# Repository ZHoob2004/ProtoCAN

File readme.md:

# ProtoCAN
A simple CAN interface for breadboards using MCP2515 controller and MCP2562 transciever.

(formerly canbus)

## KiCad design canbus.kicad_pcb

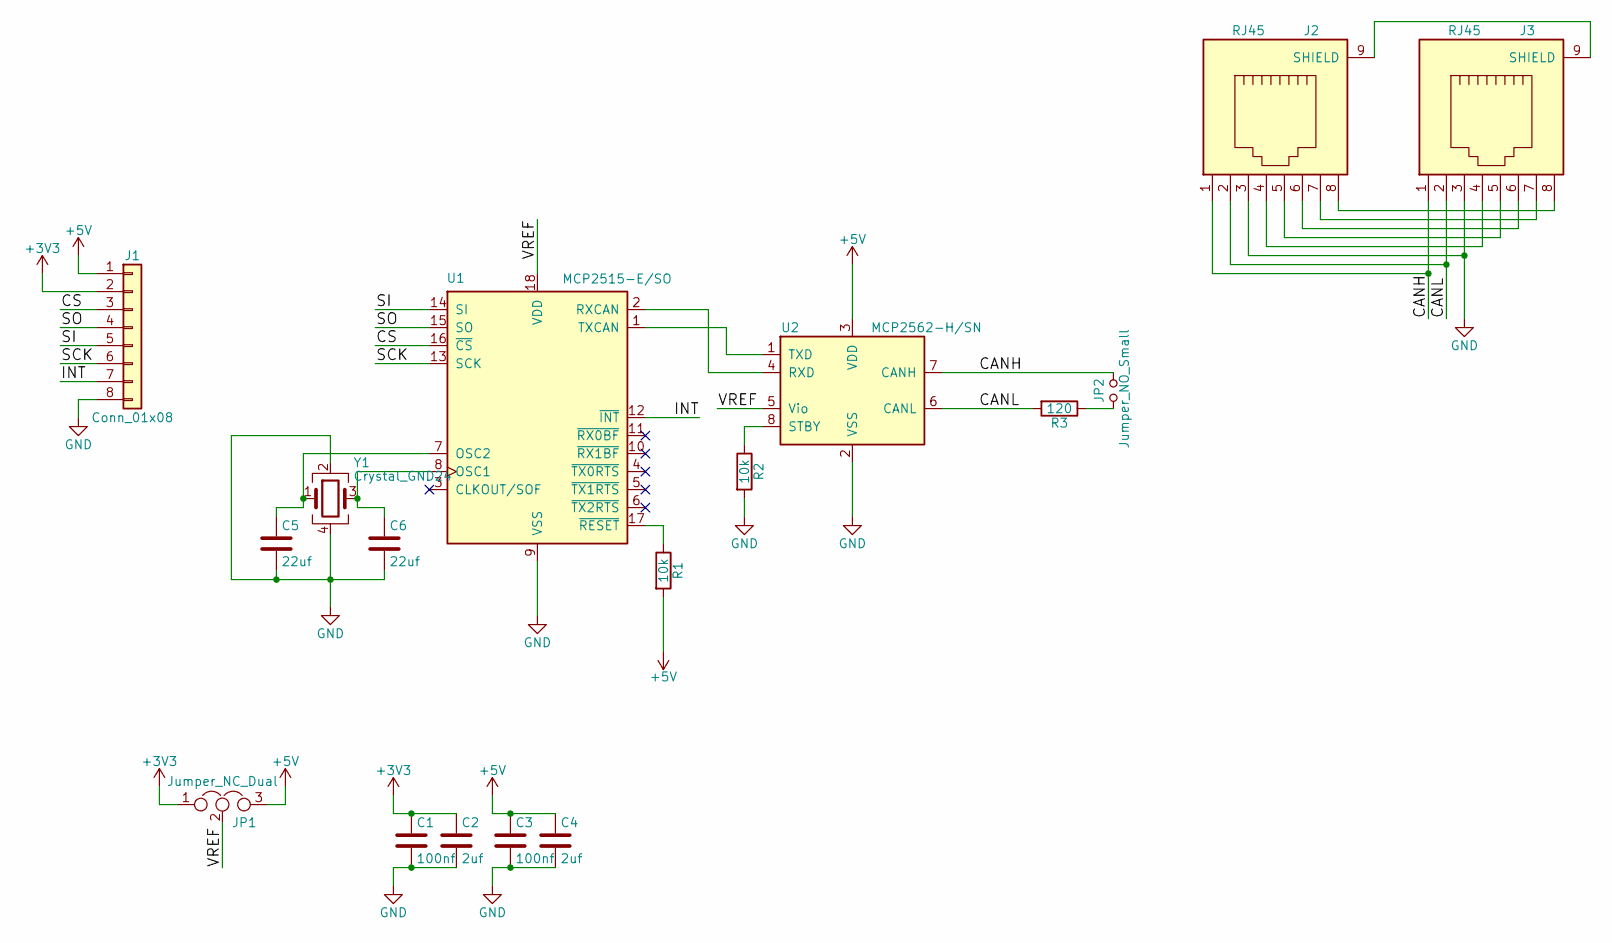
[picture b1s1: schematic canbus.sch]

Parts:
C1, C3: 100nf; C_0805_HandSoldering
C2, C4: 2uf; C_0805_HandSoldering
C5, C6: 22uf; C_0805_HandSoldering
J1: Conn_01x08; Pin_Header_Straight_1x08_Pitch2.54mm
J2, J3: RJ45; RJ45_8
JP1: Jumper_NC_Dual; Pin_Header_Straight_1x03_Pitch2.54mm
JP2: Jumper_NO_Small; Pin_Header_Straight_1x02_Pitch2.54mm
R1, R2: 10k; R_0805_HandSoldering
R3: 120; R_0805_HandSoldering
U1: MCP2515-E/SO; SOIC-18W_7.5x11.6mm_Pitch1.27mm
U2: MCP2562-H/SN; SOIC-8_3.9x4.9mm_Pitch1.27mm
Y1: Crystal_GND24; Crystal_SMD_5032-4pin_5.0x3.2mm

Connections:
+3V3: C1.1, C2.1, J1.2, JP1.1
+5V: C3.1, C4.1, J1.1, JP1.3, R1.2, U2.3 (VDD)
/CANH: J2.1, J3.1, JP2.2, U2.7 (CANH)
/CANL: J2.2, J3.2, R3.2, U2.6 (CANL)
/CS: J1.3, U1.16 (~CS)
/INT: J1.7, U1.12 (~INT)
/SCK: J1.6, U1.13 (SCK)
/SI: J1.5, U1.14 (SI)
/SO: J1.4, U1.15 (SO)
/VREF: JP1.2, U1.18 (VDD), U2.5 (Vio)
GND: C1.2, C2.2, C3.2, C4.2, C5.2, C6.2, J1.8, J2.3, J3.3, R2.2, U1.9 (VSS), U2.2 (VSS), Y1.2, Y1.4
unnamed: C5.1, U1.7 (OSC2), Y1.1
unnamed: C6.1, U1.8 (OSC1), Y1.3
unnamed: J2.4, J3.4
unnamed: J2.5, J3.5
unnamed: J2.6, J3.6
unnamed: J2.7, J3.7
unnamed: J2.8, J3.8
unnamed: JP2.1, R3.1
unnamed: R1.1, U1.17 (~RESET)
unnamed: R2.1, U2.8 (STBY)
unnamed: U1.1 (TXCAN), U2.1 (TXD)
unnamed: U1.2 (RXCAN), U2.4 (RXD)

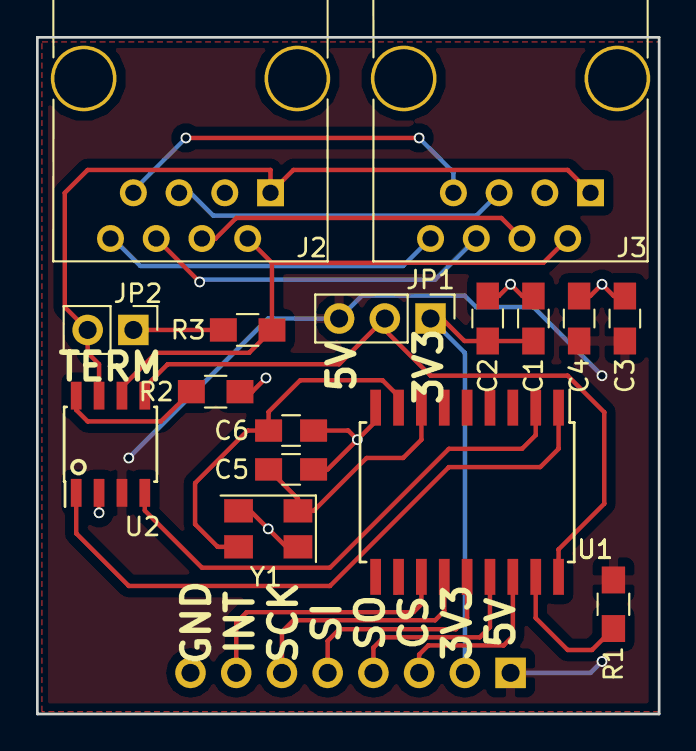
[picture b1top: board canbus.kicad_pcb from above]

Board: 2 copper layers, 34.5 x 37.6 mm, 17 parts (1 on the bottom side), 23 nets.

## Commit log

2017-10-16 Added readme.md
2017-10-16 Initial schematic draft - non-functional
2017-10-16 Added more connection - incomplete
2017-10-16 Started vref selector and main connector pins
2017-10-17 Finished schematic and component association
2017-10-17 Generated netlist
2017-10-17 Began PCB layout
2017-10-18 Board Layout finished - Should work
2017-10-18 I'm a fool who forgot to add edge cuts
2017-10-19 Changed MCP2515 to SOIC-18 - Unfinished
2017-10-19 Finished pcb layout, slightly smaller than before
2017-10-19 Adjusted silkscreen, shrank top edge
2017-11-02 add canbus.xml
2017-11-02 Corrected schematic mistakes and updated pcb to match
2017-11-02 Added SVG of schematic
2017-11-02 Flipped main connector to bottom of PCB
2017-11-02 Added 3D render of board
2017-11-02 Changed SOIC18 footprint to builtin
2017-11-03 Added gnd to RJ45 and connected all pins for passthrough
2018-05-23 Added missing capacitors for oscillator
2018-05-23 Modified layout to include capacitors for oscillator
2018-05-25 Fixed MCP2515 Reset pullup
